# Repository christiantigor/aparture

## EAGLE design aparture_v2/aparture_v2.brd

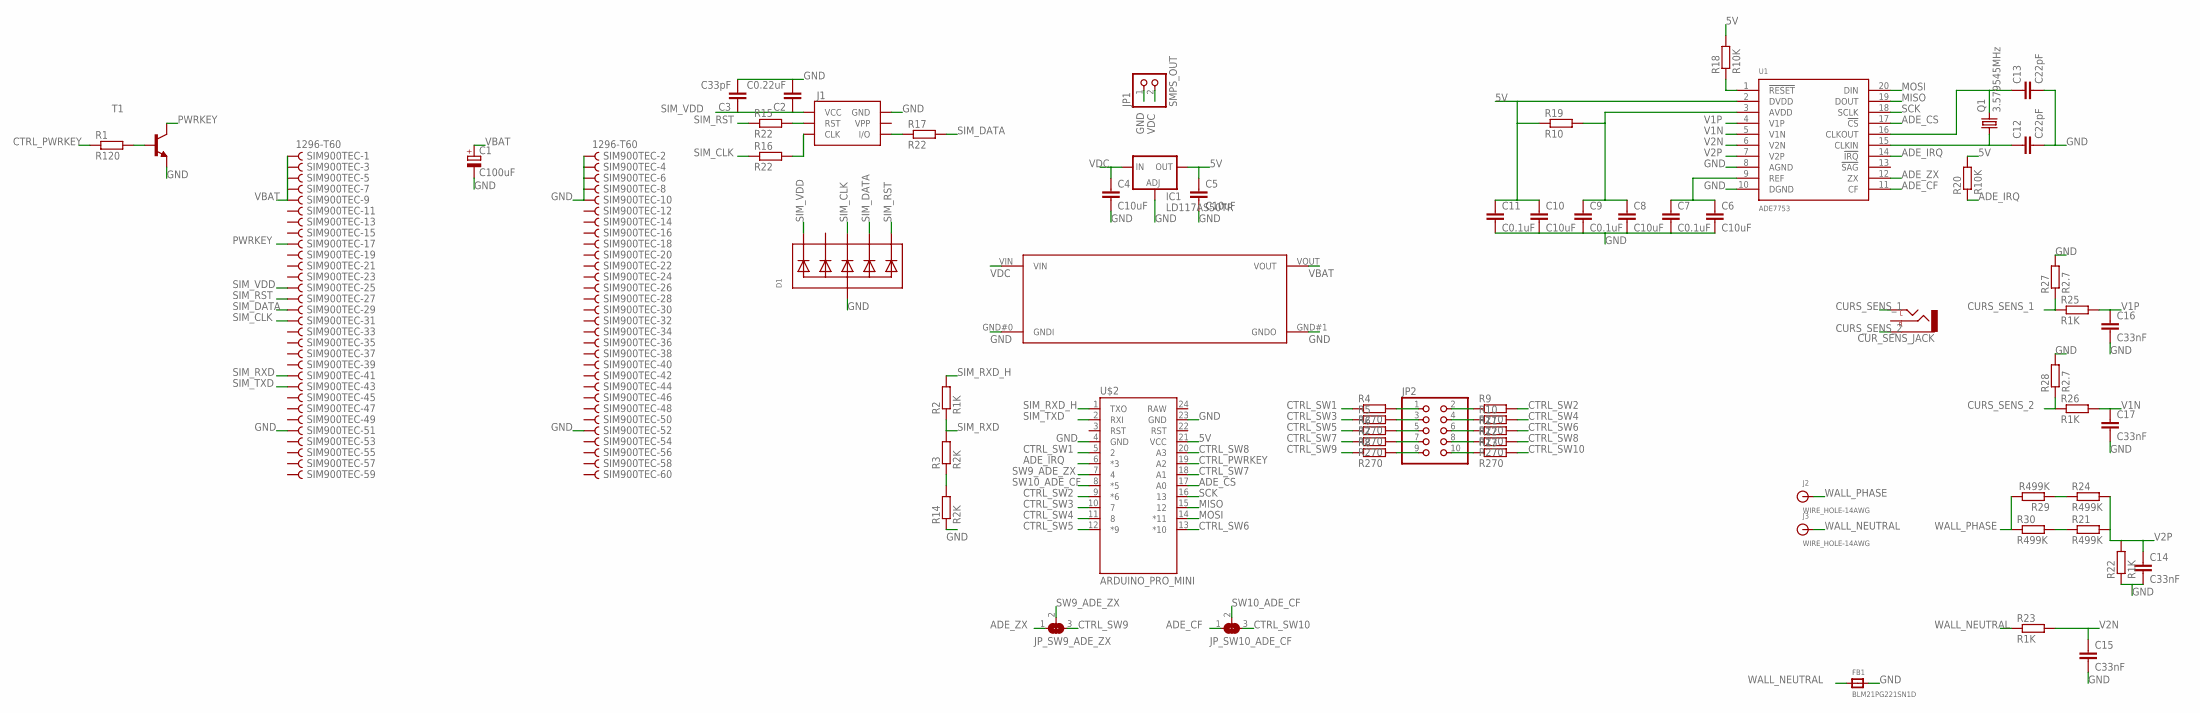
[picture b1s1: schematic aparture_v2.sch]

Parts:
C1: C100uF; 153CLV-0605
C2: C0.22uF; C0805
C3: C33pF; C0805
C4, C5, C6, C8, C10: C10uF; C0805
C7, C9, C11: C0.1uF; C0805
C12, C13: C22pF; C0805
C14, C15, C16, C17: C33nF; C0805
CUR_SENS_JACK: AUDIO-JACKSMD2; AUDIO-JACK-3.5MM-SMD
D1: TVSARRAY_5LANE; SOT363
FB1: BLM21PG221SN1D; 0805
IC1: LD117AS50TR; SOT223
J1: SIMHOLDERSIM; SIMHOLDER
J2, J3: WIRE_HOLE-14AWG
JP1: SMPS_OUT; 1X02
JP2: PINHD-2X5; 2X05
JP_SW9_ADE_ZX, JP_SW10_ADE_CF: SOLDERJUMPER_2WAY0603; SOLDERJUMPER_2WAY_OPEN_0603
Q1: 3.579545MHz; HC49/S
R1: R120; R0805
R2: R1K; M0805
R3, R14: R2K; M0805
R4, R5, R6, R7, R8, R9, R10, R11, R12, R13: R270; R0603
R15, R16, R17: R22; R0603
R18, R20: R10K; R0805
R19: R10; R0805
R21, R30: R499K; R0805
R22, R23, R25, R26: R1K; R0805
R24, R29: R499K; 0309V
R27, R28: R2.7; 0309V
SIM900TEC: 1296-T60; 1296-60
T1: MMBT2222ALT1-NPN-SOT23-BEC; SOT23-BEC
U1: ADE7753; SSOP-20
U$1: DCDCMODULE
U$2: ARDUINO_PRO_MINI

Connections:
5V: C5.1, C10.1, C11.1, IC1.4 (OUT), R18.2, R19.1, R20.2, U1.2 (DVDD), U$2.21 (VCC)
ADE_CF: JP_SW10_ADE_CF.1, U1.11 (CF)
ADE_CS: U1.17 (!CS), U$2.17 (A0)
ADE_IRQ: R20.1, U1.14 (!IRQ), U$2.6 (*3)
ADE_ZX: JP_SW9_ADE_ZX.1, U1.12 (ZX)
CTRL_PWRKEY: R1.1, U$2.19 (A2)
CTRL_SW1: R4.1, U$2.5 (2)
CTRL_SW2: R9.2, U$2.9 (*6)
CTRL_SW3: R5.1, U$2.10 (7)
CTRL_SW4: R10.2, U$2.11 (8)
CTRL_SW5: R6.1, U$2.12 (*9)
CTRL_SW6: R11.2, U$2.13 (*10)
CTRL_SW7: R7.1, U$2.18 (A1)
CTRL_SW8: R12.2, U$2.20 (A3)
CTRL_SW9: JP_SW9_ADE_ZX.3, R8.1
CTRL_SW10: JP_SW10_ADE_CF.3, R13.2
CURS_SENS_1: CUR_SENS_JACK.TIP (LEFT), R25.1, R27.1
CURS_SENS_2: CUR_SENS_JACK.SLEEVE, R26.1, R28.1
GND: C1.-, C2.2, C3.2, C4.2, C5.2, C6.2, C7.2, C8.2, C9.2, C10.2, C11.2, C12.2, C13.2, C14.2, C15.2, C16.2, C17.2, D1.2 (A), FB1.2, IC1.1 (ADJ), J1.C5 (GND), JP1.1, R14.1, R22.1, R27.2, R28.2, SIM900TEC.2, SIM900TEC.4, SIM900TEC.6, SIM900TEC.8, SIM900TEC.10, SIM900TEC.51, SIM900TEC.52, T1.E, U1.8 (AGND), U1.10 (DGND), U$1.GND#0 (GNDI), U$1.GND#1 (GNDO), U$2.4 (GND), U$2.23 (GND)
MISO: U1.19 (DOUT), U$2.15 (12)
MOSI: U1.20 (DIN), U$2.14 (*11)
unnamed: R1.2, T1.B
unnamed: JP2.1, R4.2
unnamed: JP2.3, R5.2
unnamed: JP2.5, R6.2
unnamed: JP2.7, R7.2
unnamed: R24.1, R29.1
unnamed: JP2.2, R9.1
unnamed: JP2.4, R10.1
unnamed: JP2.6, R11.1
unnamed: JP2.8, R12.1
unnamed: JP2.9, R8.2
unnamed: R3.1, R14.2
unnamed: J1.C2 (RST), R15.2
unnamed: J1.C3 (CLK), R16.2
unnamed: J1.C7 (I/O), R17.1
unnamed: R18.1, U1.1 (!RESET)
unnamed: C6.1, C7.1, U1.9 (REF)
unnamed: C8.1, C9.1, R19.2, U1.3 (AVDD)
unnamed: C12.1, Q1.1, U1.15 (CLKIN)
unnamed: C13.1, Q1.2, U1.16 (CLKOUT)
unnamed: JP2.10, R13.1
unnamed: R21.1, R30.2
PWRKEY: SIM900TEC.17, T1.C
SCK: U1.18 (SCLK), U$2.16 (13)
SIM_CLK: D1.4 (C3), R16.1, SIM900TEC.31
SIM_DATA: D1.5 (C4), R17.2, SIM900TEC.29
SIM_RST: D1.6 (C5), R15.1, SIM900TEC.27
SIM_RXD: R2.1, R3.2, SIM900TEC.41
SIM_RXD_H: R2.2, U$2.1 (TXO)
SIM_TXD: SIM900TEC.43, U$2.2 (RXI)
SIM_VDD: C2.1, C3.1, D1.1 (C1), J1.C1 (VCC), SIM900TEC.25
SW9_ADE_ZX: JP_SW9_ADE_ZX.2, U$2.7 (4)
SW10_ADE_CF: JP_SW10_ADE_CF.2, U$2.8 (*5)
V1N: C17.1, R26.2, U1.5 (V1N)
V1P: C16.1, R25.2, U1.4 (V1P)
V2N: C15.1, R23.2, U1.6 (V2N)
V2P: C14.1, R21.2, R22.2, R24.2, U1.7 (V2P)
VBAT: C1.+, SIM900TEC.1, SIM900TEC.3, SIM900TEC.5, SIM900TEC.7, SIM900TEC.9, U$1.VOUT
VDC: C4.1, IC1.3 (IN), JP1.2, U$1.VIN
WALL_NEUTRAL: FB1.1, J3.P$1, R23.1
WALL_PHASE: J2.P$1, R29.2, R30.1

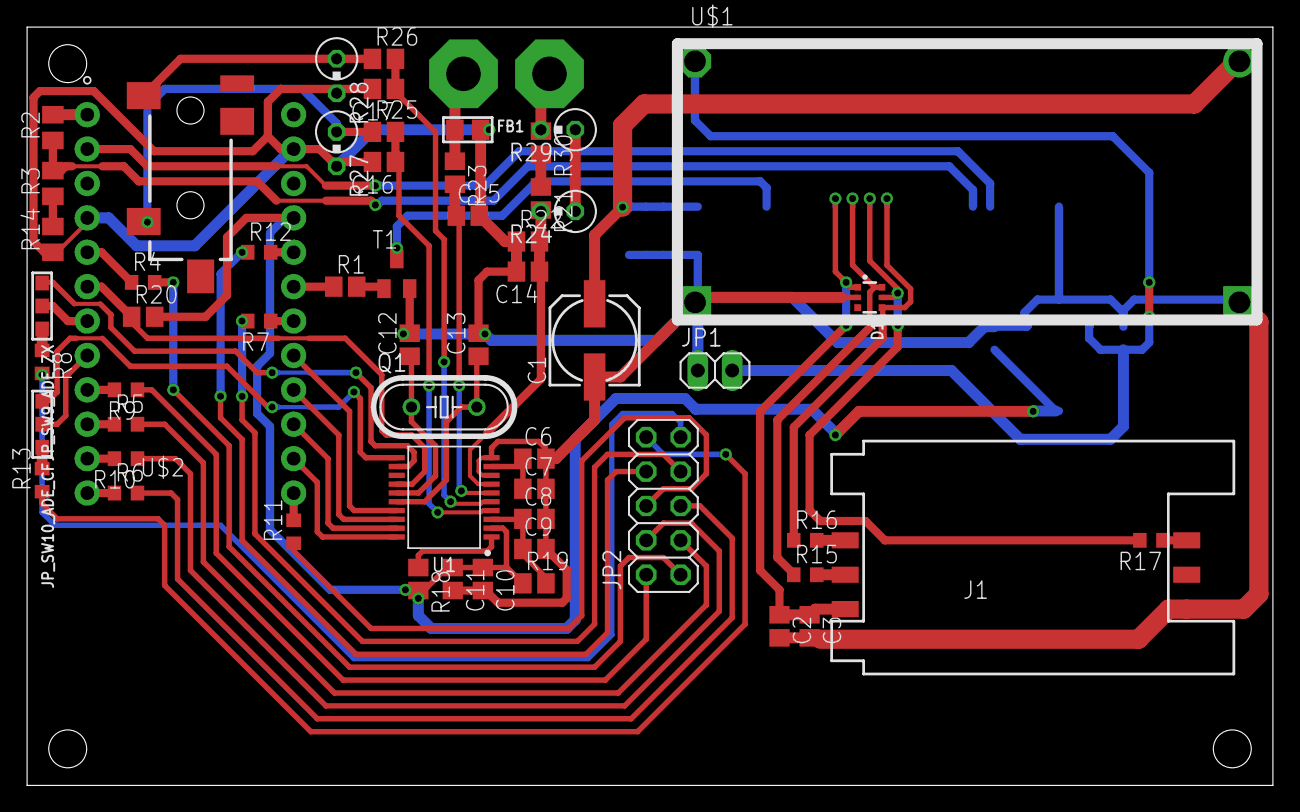
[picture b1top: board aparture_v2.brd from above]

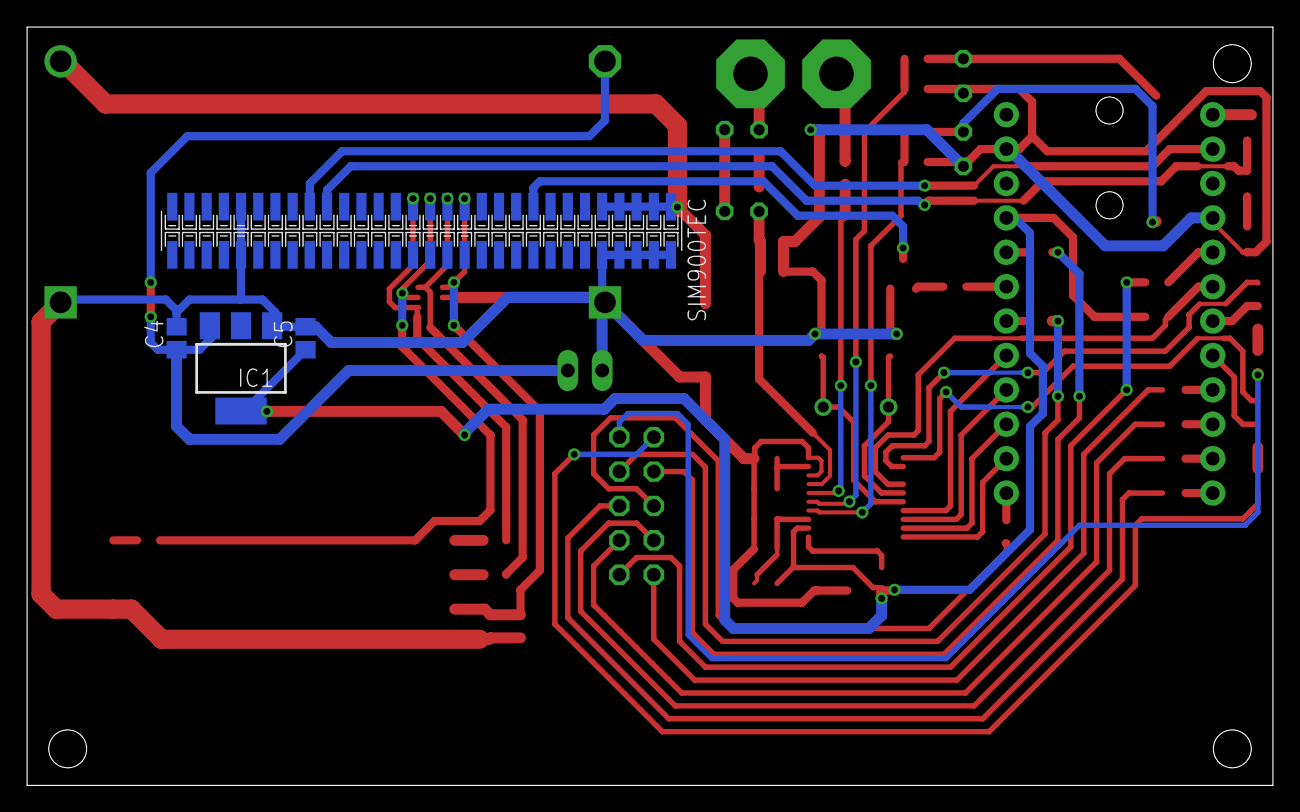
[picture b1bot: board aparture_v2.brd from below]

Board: 2 copper layers, 92.0 x 56.0 mm, 64 parts (4 on the bottom side), 62 nets.

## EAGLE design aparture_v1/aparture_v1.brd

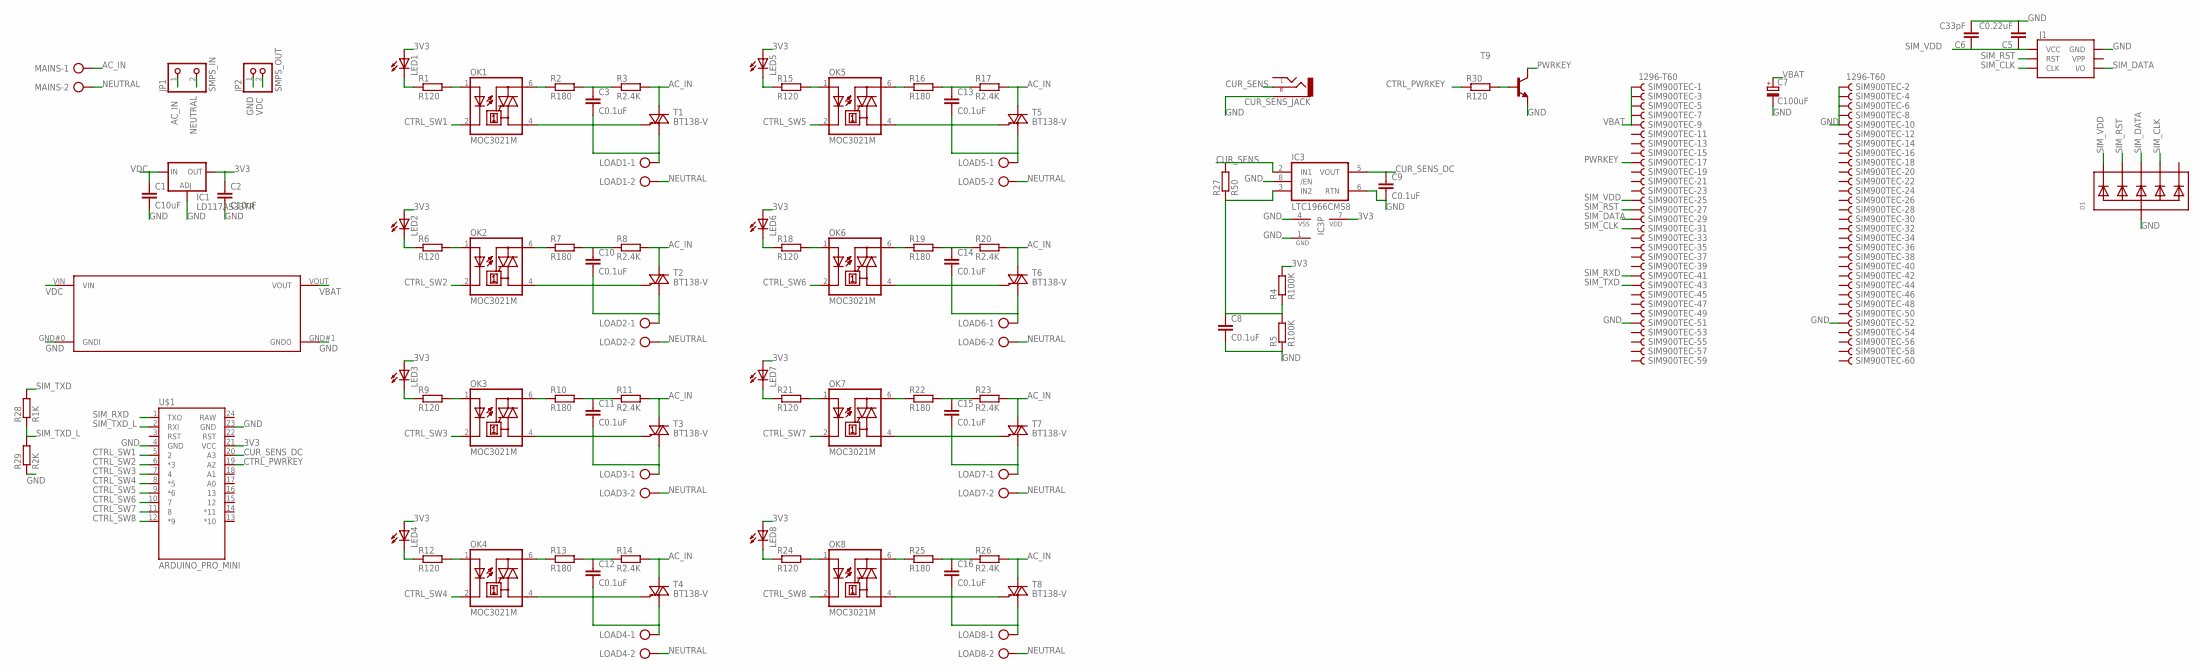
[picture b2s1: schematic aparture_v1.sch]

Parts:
C1, C2: C10uF; C0805
C3, C8, C9, C10, C11, C12, C13, C14, C15, C16: C0.1uF; C0805
C5: C0.22uF; C0805
C6: C33pF; C0805
C7: C100uF; 153CLV-0605
CUR_SENS_JACK: AUDIO-JACKSMD2; AUDIO-JACK-3.5MM-SMD
D1: TVSARRAY_5LANE; SOT363
IC1: LD117AS33TR; SOT223
IC3: LTC1966CMS8; MSOP8
J1: SIMHOLDERSIM; SIMHOLDER
JP1: SMPS_IN
JP2: SMPS_OUT; 1X02
LED1, LED2, LED3, LED4, LED5, LED6, LED7, LED8: LED3MM
LOAD1, LOAD2, LOAD3, LOAD4, LOAD5, LOAD6, LOAD7, LOAD8: AK300/2
MAINS: AK300/2
OK1, OK2, OK3, OK4, OK5, OK6, OK7, OK8: MOC3021M; DIL06
R1, R6, R9, R12, R15, R18, R21, R24, R30: R120; M0805
R2, R7, R10, R13, R16, R19, R22, R25: R180; M0805
R3, R8, R11, R14, R17, R20, R23, R26: R2.4K; M0805
R4, R5: R100K; M0805
R27: R50; M0805
R28: R1K; M0805
R29: R2K; M0805
SIM900TEC: 1296-T60; 1296-60
T1, T2, T3, T4, T5, T6, T7, T8: BT138-V; TO220BV
T9: MMBT2222ALT1-NPN-SOT23-BEC; SOT23-BEC
U$1: ARDUINO_PRO_MINI
VOL_REG_SIM900: DCDCMODULE

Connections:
3V3: C2.1, IC1.4 (OUT), IC3.7 (VDD), LED1.A, LED2.A, LED3.A, LED4.A, LED5.A, LED6.A, LED7.A, LED8.A, R4.2, U$1.21 (VCC)
AC_IN: JP1.1, MAINS.1, R3.2, R8.2, R11.2, R14.2, R17.2, R20.2, R23.2, R26.2, T1.T2 (A2), T2.T2 (A2), T3.T2 (A2), T4.T2 (A2), T5.T2 (A2), T6.T2 (A2), T7.T2 (A2), T8.T2 (A2)
CTRL_PWRKEY: R30.1, U$1.19 (A2)
CTRL_SW1: OK1.2 (C), U$1.5 (2)
CTRL_SW2: OK2.2 (C), U$1.6 (*3)
CTRL_SW3: OK3.2 (C), U$1.7 (4)
CTRL_SW4: OK4.2 (C), U$1.8 (*5)
CTRL_SW5: OK5.2 (C), U$1.9 (*6)
CTRL_SW6: OK6.2 (C), U$1.10 (7)
CTRL_SW7: OK7.2 (C), U$1.11 (8)
CTRL_SW8: OK8.2 (C), U$1.12 (*9)
CUR_SENS: CUR_SENS_JACK.RING (RIGHT), IC3.2 (IN1), R27.2
CUR_SENS_DC: C9.1, IC3.5 (VOUT), U$1.20 (A3)
GND: C1.2, C2.2, C5.2, C6.2, C7.-, C8.2, C9.2, CUR_SENS_JACK.SLEEVE, D1.2 (A), IC1.1 (ADJ), IC3.1 (GND), IC3.4 (VSS), IC3.6 (RTN), IC3.8 (/EN), J1.C5 (GND), JP2.1, R5.1, R29.1, SIM900TEC.2, SIM900TEC.4, SIM900TEC.6, SIM900TEC.8, SIM900TEC.10, SIM900TEC.51, SIM900TEC.52, T9.E, U$1.4 (GND), U$1.23 (GND), VOL_REG_SIM900.GND#0 (GNDI), VOL_REG_SIM900.GND#1 (GNDO)
unnamed: LED1.K (C), R1.1
unnamed: OK1.1 (A), R1.2
unnamed: OK1.6 (A2), R2.1
unnamed: C3.1, R2.2, R3.1
unnamed: OK1.4 (A1), T1.G
unnamed: C3.2, LOAD1.1, T1.T1 (A1)
unnamed: C8.1, IC3.3 (IN2), R4.1, R5.2, R27.1
unnamed: R30.2, T9.B
unnamed: LED2.K (C), R6.1
unnamed: OK2.1 (A), R6.2
unnamed: OK2.6 (A2), R7.1
unnamed: C10.1, R7.2, R8.1
unnamed: OK2.4 (A1), T2.G
unnamed: C10.2, LOAD2.1, T2.T1 (A1)
unnamed: LED3.K (C), R9.1
unnamed: OK3.1 (A), R9.2
unnamed: OK3.6 (A2), R10.1
unnamed: C11.1, R10.2, R11.1
unnamed: OK3.4 (A1), T3.G
unnamed: C11.2, LOAD3.1, T3.T1 (A1)
unnamed: LED4.K (C), R12.1
unnamed: OK4.1 (A), R12.2
unnamed: OK4.6 (A2), R13.1
unnamed: C12.1, R13.2, R14.1
unnamed: OK4.4 (A1), T4.G
unnamed: C12.2, LOAD4.1, T4.T1 (A1)
unnamed: LED5.K (C), R15.1
unnamed: OK5.1 (A), R15.2
unnamed: OK5.6 (A2), R16.1
unnamed: C13.1, R16.2, R17.1
unnamed: OK5.4 (A1), T5.G
unnamed: C13.2, LOAD5.1, T5.T1 (A1)
unnamed: LED6.K (C), R18.1
unnamed: OK6.1 (A), R18.2
unnamed: OK6.6 (A2), R19.1
unnamed: C14.1, R19.2, R20.1
unnamed: OK6.4 (A1), T6.G
unnamed: C14.2, LOAD6.1, T6.T1 (A1)
unnamed: LED7.K (C), R21.1
unnamed: OK7.1 (A), R21.2
unnamed: OK7.6 (A2), R22.1
unnamed: C15.1, R22.2, R23.1
unnamed: OK7.4 (A1), T7.G
unnamed: C15.2, LOAD7.1, T7.T1 (A1)
unnamed: LED8.K (C), R24.1
unnamed: OK8.1 (A), R24.2
unnamed: OK8.6 (A2), R25.1
unnamed: C16.1, R25.2, R26.1
unnamed: OK8.4 (A1), T8.G
unnamed: C16.2, LOAD8.1, T8.T1 (A1)
NEUTRAL: JP1.2, LOAD1.2, LOAD2.2, LOAD3.2, LOAD4.2, LOAD5.2, LOAD6.2, LOAD7.2, LOAD8.2, MAINS.2
PWRKEY: SIM900TEC.17, T9.C
SIM_CLK: D1.5 (C4), J1.C3 (CLK), SIM900TEC.31
SIM_DATA: D1.4 (C3), J1.C7 (I/O), SIM900TEC.29
SIM_RST: D1.3 (C2), J1.C2 (RST), SIM900TEC.27
SIM_RXD: SIM900TEC.41, U$1.1 (TXO)
SIM_TXD: R28.2, SIM900TEC.43
SIM_TXD_L: R28.1, R29.2, U$1.2 (RXI)
SIM_VDD: C5.1, C6.1, D1.1 (C1), J1.C1 (VCC), SIM900TEC.25
VBAT: C7.+, SIM900TEC.1, SIM900TEC.3, SIM900TEC.5, SIM900TEC.7, SIM900TEC.9, VOL_REG_SIM900.VOUT
VDC: C1.1, IC1.3 (IN), JP2.2, VOL_REG_SIM900.VIN

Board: 2 copper layers, 89 parts (0 on the bottom side), 75 nets, no tracks yet.

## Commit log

2014-10-13 :lollipop: Added .gitattributes & .gitignore files
2014-10-13 Add pcb schematic
2014-10-30 Add sch and finish pcb ver 2

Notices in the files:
parts and their libraries:
SparkFun-Connectors: Licensing: Creative Commons ShareAlike 4.0 International - https://creativecommons.org/licenses/by-sa/4.0
microbuilder: This work is placed in the public domain, and may be freely used for commercial and non-commercial work with the following conditions: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
